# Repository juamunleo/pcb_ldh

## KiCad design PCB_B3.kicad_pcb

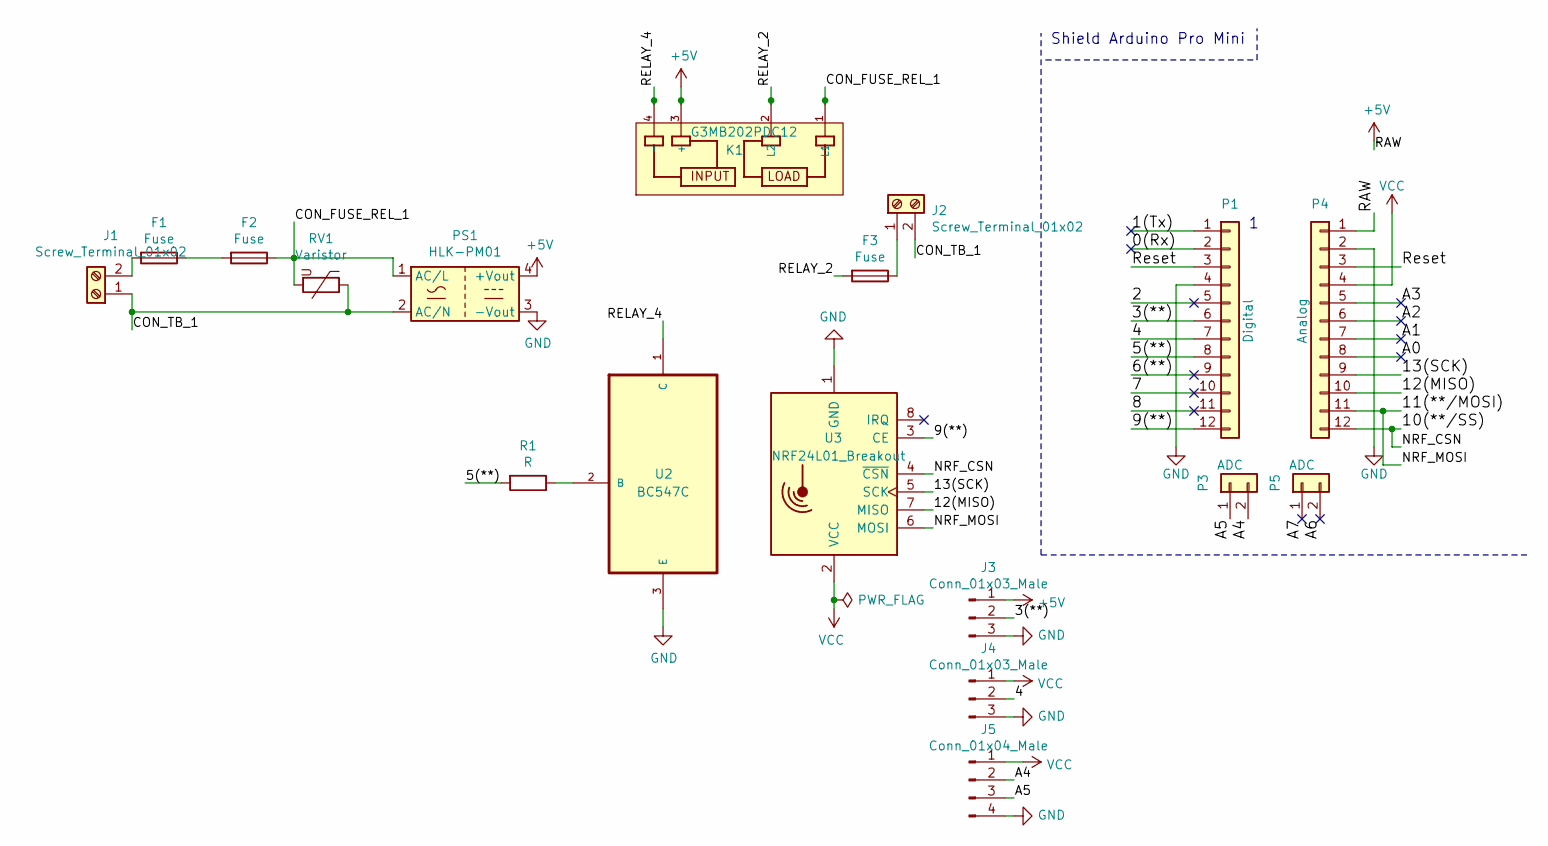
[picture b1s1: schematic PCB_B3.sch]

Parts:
F1, F2, F3: Fuse; R_Axial_DIN0414_L11.9mm_D4.5mm_P15.24mm_Horizontal
J1, J2: Screw_Terminal_01x02; TerminalBlock_Altech_AK300-2_P5.00mm
J3, J4: Conn_01x03_Male; PinHeader_1x03_P2.54mm_Vertical
J5: Conn_01x04_Male; PinHeader_1x04_P2.54mm_Vertical
K1: G3MB202PDC12; RELAY_G3MB202PDC12; PARTREV N/A
P1: Digital; Socket_Strip_Arduino_1x12
P3, P5: ADC; Socket_Strip_Arduino_1x02
P4: Analog; Socket_Strip_Arduino_1x12
PS1: HLK-PM01; Converter_ACDC_HiLink_HLK-PMxx
R1: R; R_1206_3216Metric_Pad1.30x1.75mm_HandSolder
RV1: Varistor; RV_Disc_D12mm_W6.2mm_P7.5mm
U2: BC547C; MPN BC547C
U3: NRF24L01_Breakout; nRF24L01_Breakout

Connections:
+5V: J3.1, K1.3 (+), P4.1, PS1.4 (+Vout)
/0(Rx): P1.2
/1(Tx): P1.1
/2: P1.5
/3(**): J3.2, P1.6
/4: J4.2, P1.7
/5(**): P1.8, R1.2
/6(**): P1.9
/7: P1.10
/8: P1.11
/9(**): P1.12, U3.3 (CE)
/10(**/SS): P4.12, U3.4 (~CSN)
/11(**/MOSI): P4.11, U3.6 (MOSI)
/12(MISO): P4.10, U3.7 (MISO)
/13(SCK): P4.9, U3.5 (SCK)
/A0: P4.8
/A1: P4.7
/A2: P4.6
/A3: P4.5
/A4: J5.2, P3.2
/A5: J5.3, P3.1
/A6: P5.2
/A7: P5.1
/CON_FUSE_REL_1: F2.1, K1.1 (L1), PS1.1 (AC/L), RV1.2
/CON_TB_1: J1.1, J2.2, PS1.2 (AC/N), RV1.1
/RELAY_2: F3.2, K1.2 (L2)
/RELAY_4: K1.4 (-), U2.1 (C)
/Reset: P1.3, P4.3
GND: J3.3, J4.3, J5.4, P1.4, P4.2, PS1.3 (-Vout), U2.3 (E), U3.1 (GND)
unnamed: F1.1, F2.2
unnamed: F1.2, J1.2
unnamed: F3.1, J2.1
unnamed: R1.1, U2.2 (B)
VCC: J4.1, J5.1, P4.4, U3.2 (VCC)

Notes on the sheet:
Shield Arduino Pro Mini

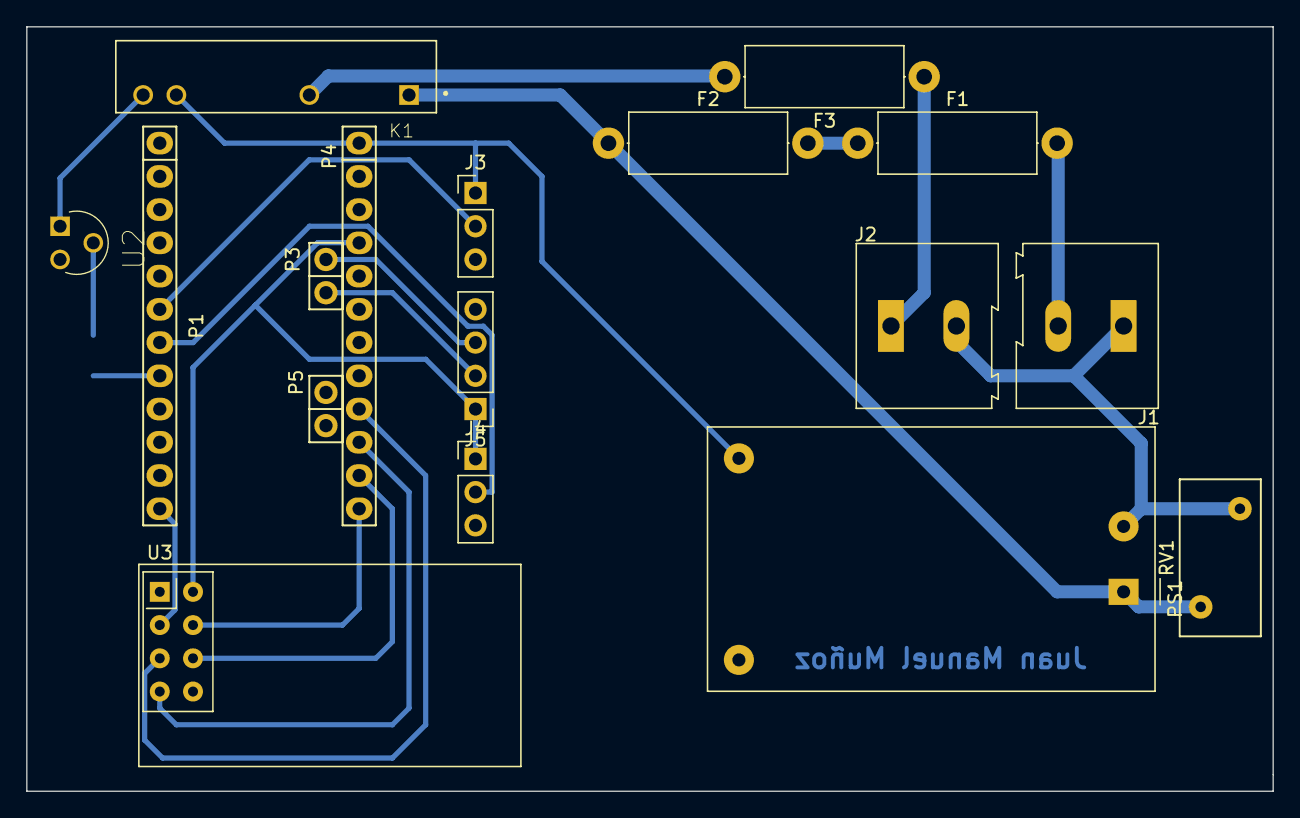
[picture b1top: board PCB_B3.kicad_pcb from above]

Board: 2 copper layers, 95.2 x 58.4 mm, 18 parts (1 on the bottom side), 22 nets.
